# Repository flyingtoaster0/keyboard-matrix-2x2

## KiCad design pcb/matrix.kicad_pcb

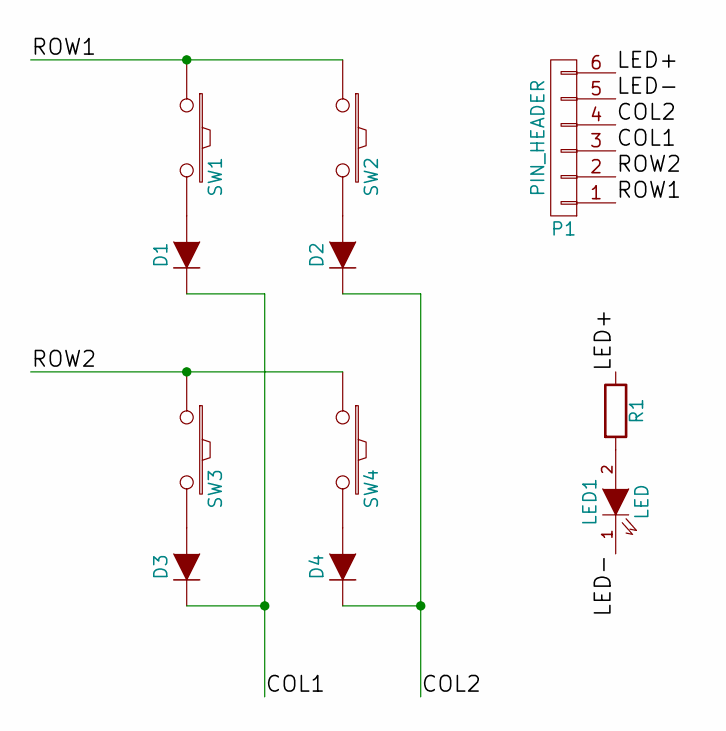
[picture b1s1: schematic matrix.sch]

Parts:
D1, D2, D3, D4: D; SOD-123
LED1: LED; CHERRY_MX_LED
P1: PIN_HEADER; Pin_Header_Straight_1x06
R1: R; Resistor_Horizontal_RM10mm
SW1, SW2, SW3, SW4: SW_PUSH; CHERRY_PLATE_100H

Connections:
/COL1: D1.1 (K), D3.1 (K), P1.3
/COL2: D2.1 (K), D4.1 (K), P1.4
/LED+: P1.6, R1.1
/LED-: LED1.1 (K), P1.5
/ROW1: P1.1, SW1.1, SW2.1
/ROW2: P1.2, SW3.1, SW4.1
unnamed: D1.2 (A), SW1.2
unnamed: D2.2 (A), SW2.2
unnamed: D3.2 (A), SW3.2
unnamed: D4.2 (A), SW4.2
unnamed: LED1.2 (A), R1.2

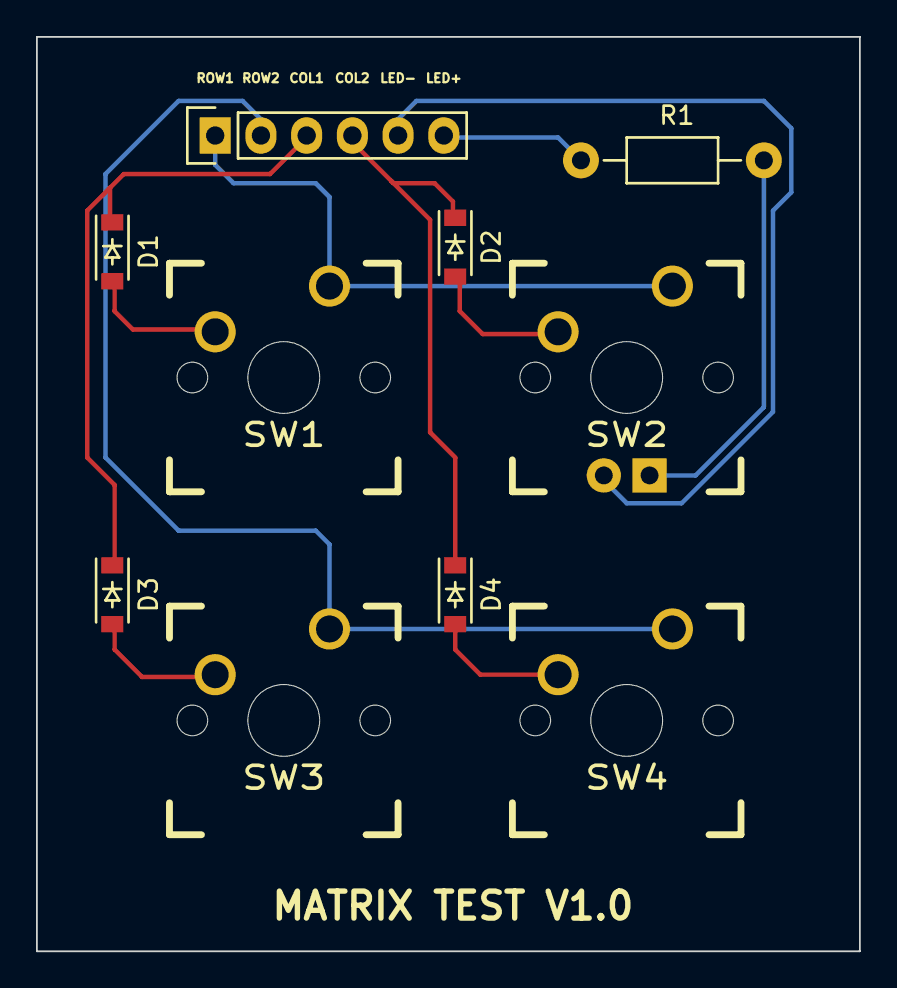
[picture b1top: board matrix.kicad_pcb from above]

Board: 2 copper layers, 45.7 x 50.8 mm, 11 parts (0 on the bottom side), 11 nets.

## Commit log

2016-09-14 Add directories, add docs
